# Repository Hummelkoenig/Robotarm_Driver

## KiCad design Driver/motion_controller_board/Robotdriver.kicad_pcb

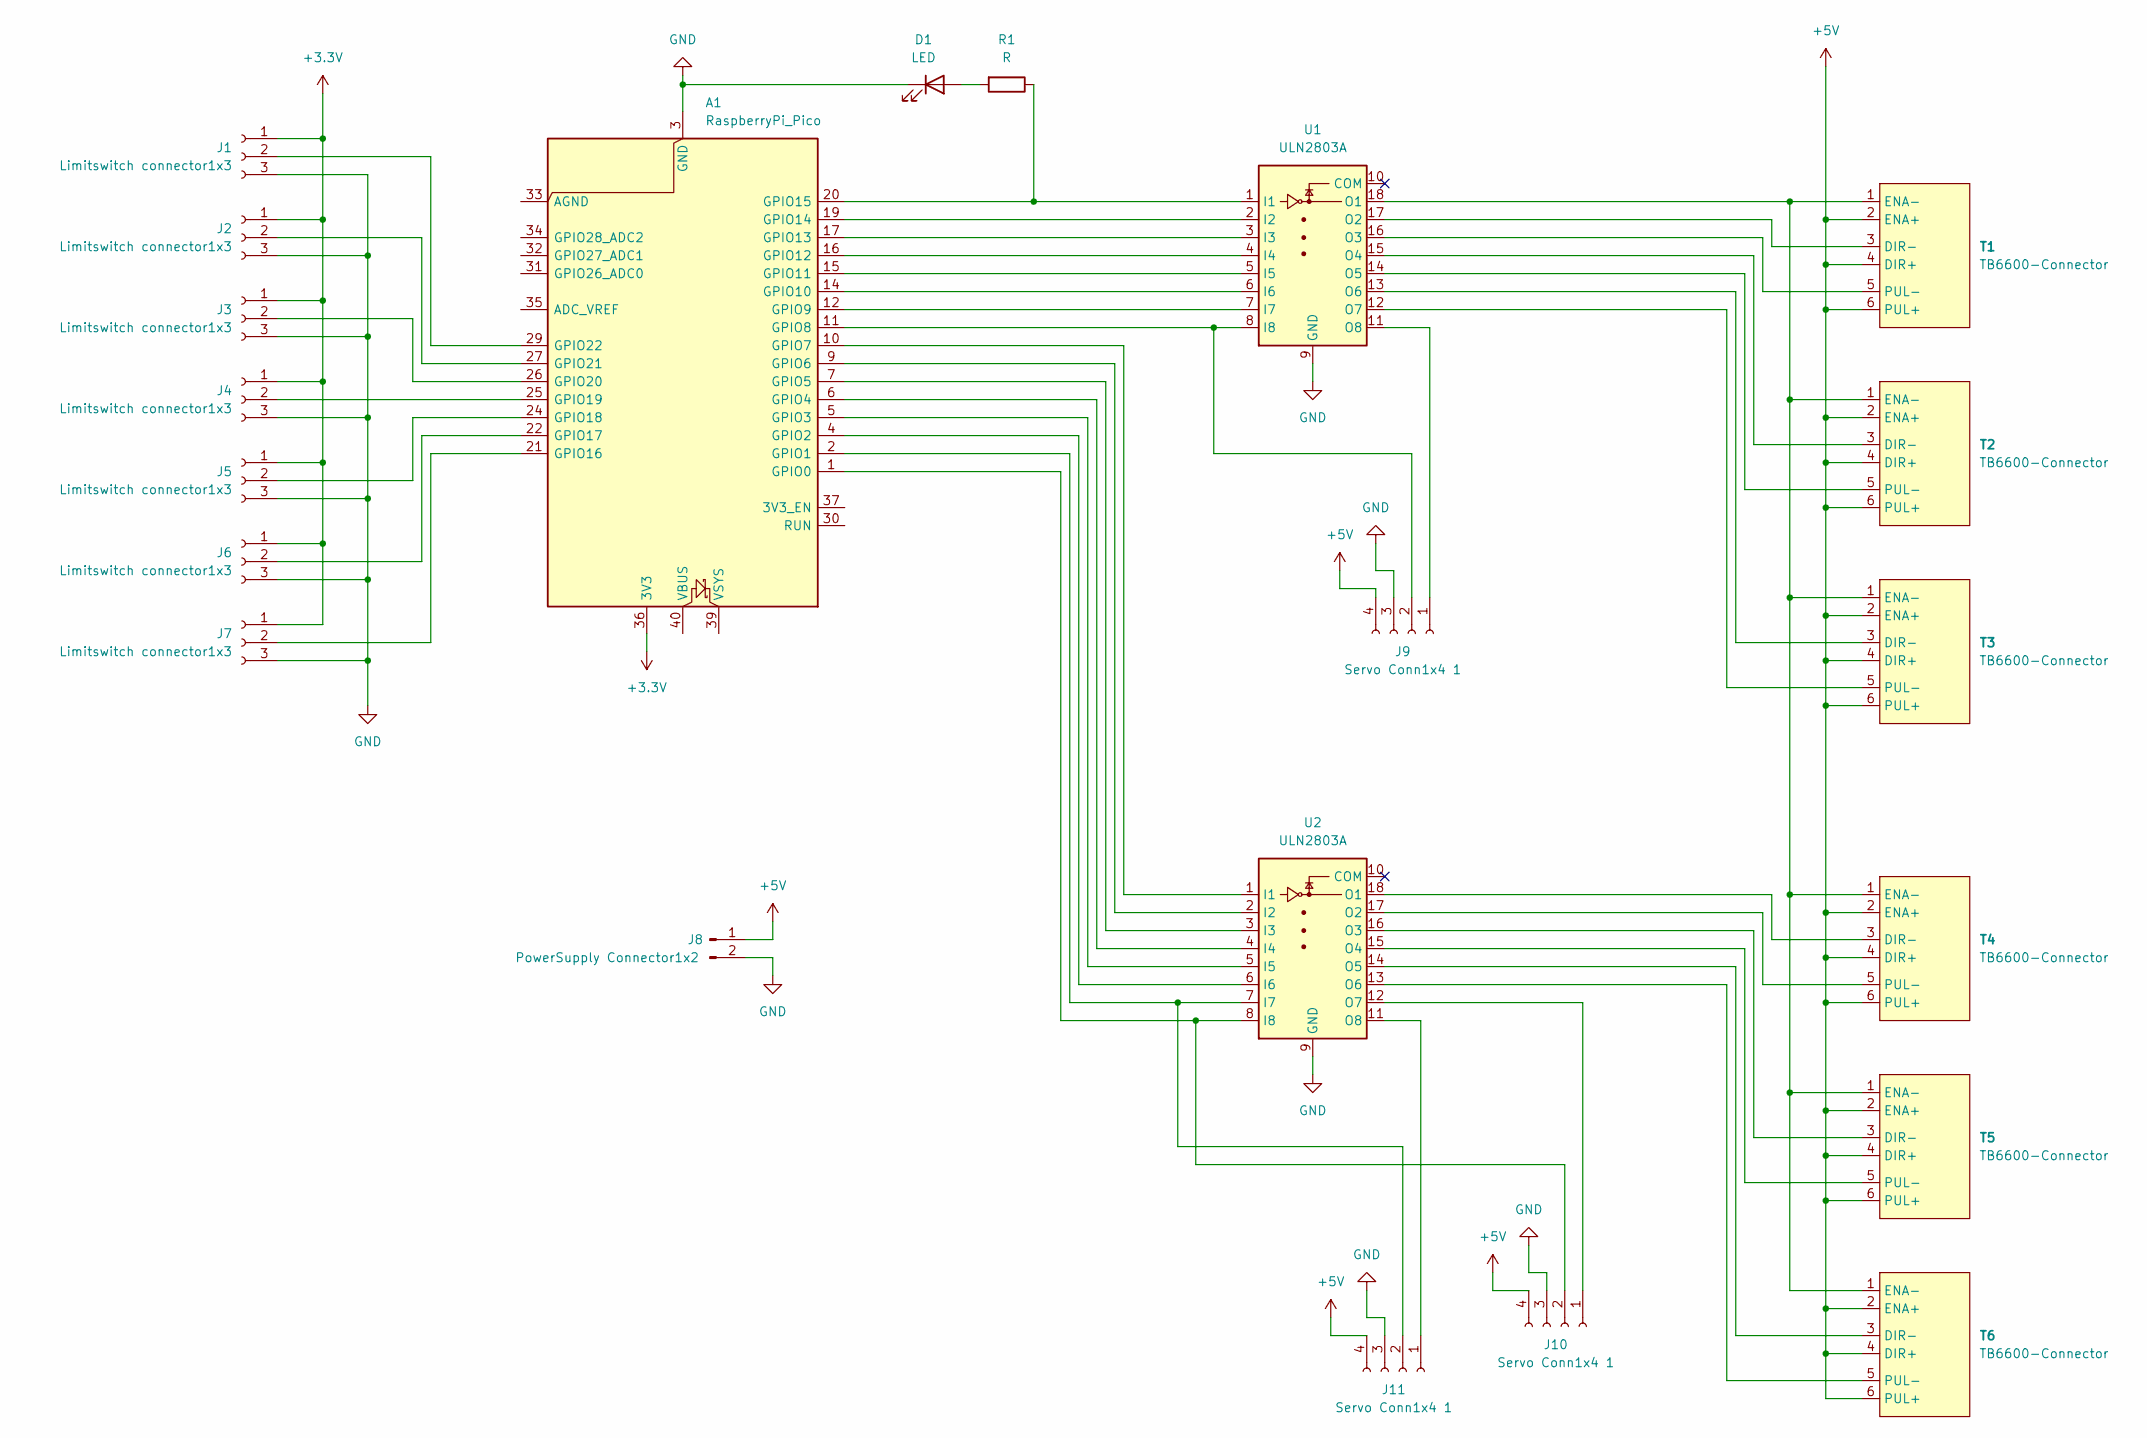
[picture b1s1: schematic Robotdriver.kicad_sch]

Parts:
A1: RaspberryPi_Pico; RaspberryPi_Pico_Common_Unspecified
D1: LED; LED_D5.0mm
J1, J2, J3, J4, J5, J6, J7: Limitswitch connector1x3; JST_EH_B3B-EH-A_1x03_P2.50mm_Vertical
J8: PowerSupply Connector1x2; JST_EH_B2B-EH-A_1x02_P2.50mm_Vertical
J9, J10, J11: Servo Conn1x4 1; JST_EH_B4B-EH-A_1x04_P2.50mm_Vertical
R1: R; R_Axial_DIN0516_L15.5mm_D5.0mm_P20.32mm_Horizontal
T1, T2, T3, T4, T5, T6: TB6600-Connector; JST_EH_B6B-EH-A_1x06_P2.50mm_Vertical
U1, U2: ULN2803A; CERDIP-18_W7.62mm_SideBrazed

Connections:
+3.3V: A1.36 (3V3), J1.1, J2.1, J3.1, J4.1, J5.1, J6.1, J7.1
+5V: J8.1, J9.4, J10.4, J11.4, T1.2 (ENA+), T1.4 (DIR+), T1.6 (PUL+), T2.2 (ENA+), T2.4 (DIR+), T2.6 (PUL+), T3.2 (ENA+), T3.4 (DIR+), T3.6 (PUL+), T4.2 (ENA+), T4.4 (DIR+), T4.6 (PUL+), T5.2 (ENA+), T5.4 (DIR+), T5.6 (PUL+), T6.2 (ENA+), T6.4 (DIR+), T6.6 (PUL+)
GND: A1.3 (GND), A1.8 (GND), A1.13 (GND), A1.18 (GND), A1.23 (GND), A1.28 (GND), A1.38 (GND), D1.1 (K), J1.3, J2.3, J3.3, J4.3, J5.3, J6.3, J7.3, J8.2, J9.3, J10.3, J11.3, U1.9 (GND), U2.9 (GND)
unnamed: A1.1 (GPIO0), J10.2, U2.8 (I8)
unnamed: A1.2 (GPIO1), J11.2, U2.7 (I7)
unnamed: A1.4 (GPIO2), U2.6 (I6)
unnamed: A1.5 (GPIO3), U2.5 (I5)
unnamed: A1.6 (GPIO4), U2.4 (I4)
unnamed: A1.7 (GPIO5), U2.3 (I3)
unnamed: A1.9 (GPIO6), U2.2 (I2)
unnamed: A1.10 (GPIO7), U2.1 (I1)
unnamed: A1.11 (GPIO8), J9.2, U1.8 (I8)
unnamed: A1.12 (GPIO9), U1.7 (I7)
unnamed: A1.14 (GPIO10), U1.6 (I6)
unnamed: A1.15 (GPIO11), U1.5 (I5)
unnamed: A1.16 (GPIO12), U1.4 (I4)
unnamed: A1.17 (GPIO13), U1.3 (I3)
unnamed: A1.19 (GPIO14), U1.2 (I2)
unnamed: A1.20 (GPIO15), R1.1, U1.1 (I1)
unnamed: A1.21 (GPIO16), J7.2
unnamed: A1.22 (GPIO17), J6.2
unnamed: A1.24 (GPIO18), J5.2
unnamed: A1.25 (GPIO19), J4.2
unnamed: A1.26 (GPIO20), J3.2
unnamed: A1.27 (GPIO21), J2.2
unnamed: A1.29 (GPIO22), J1.2
unnamed: D1.2 (A), R1.2
unnamed: J9.1, U1.11 (O8)
unnamed: J10.1, U2.12 (O7)
unnamed: J11.1, U2.11 (O8)
unnamed: T1.3 (DIR-), U1.17 (O2)
unnamed: T1.1 (ENA-), T2.1 (ENA-), T3.1 (ENA-), T4.1 (ENA-), T5.1 (ENA-), T6.1 (ENA-), U1.18 (O1)
unnamed: T1.5 (PUL-), U1.16 (O3)
unnamed: T2.3 (DIR-), U1.15 (O4)
unnamed: T2.5 (PUL-), U1.14 (O5)
unnamed: T3.3 (DIR-), U1.13 (O6)
unnamed: T3.5 (PUL-), U1.12 (O7)
unnamed: T4.3 (DIR-), U2.18 (O1)
unnamed: T4.5 (PUL-), U2.17 (O2)
unnamed: T5.3 (DIR-), U2.16 (O3)
unnamed: T5.5 (PUL-), U2.15 (O4)
unnamed: T6.3 (DIR-), U2.14 (O5)
unnamed: T6.5 (PUL-), U2.13 (O6)

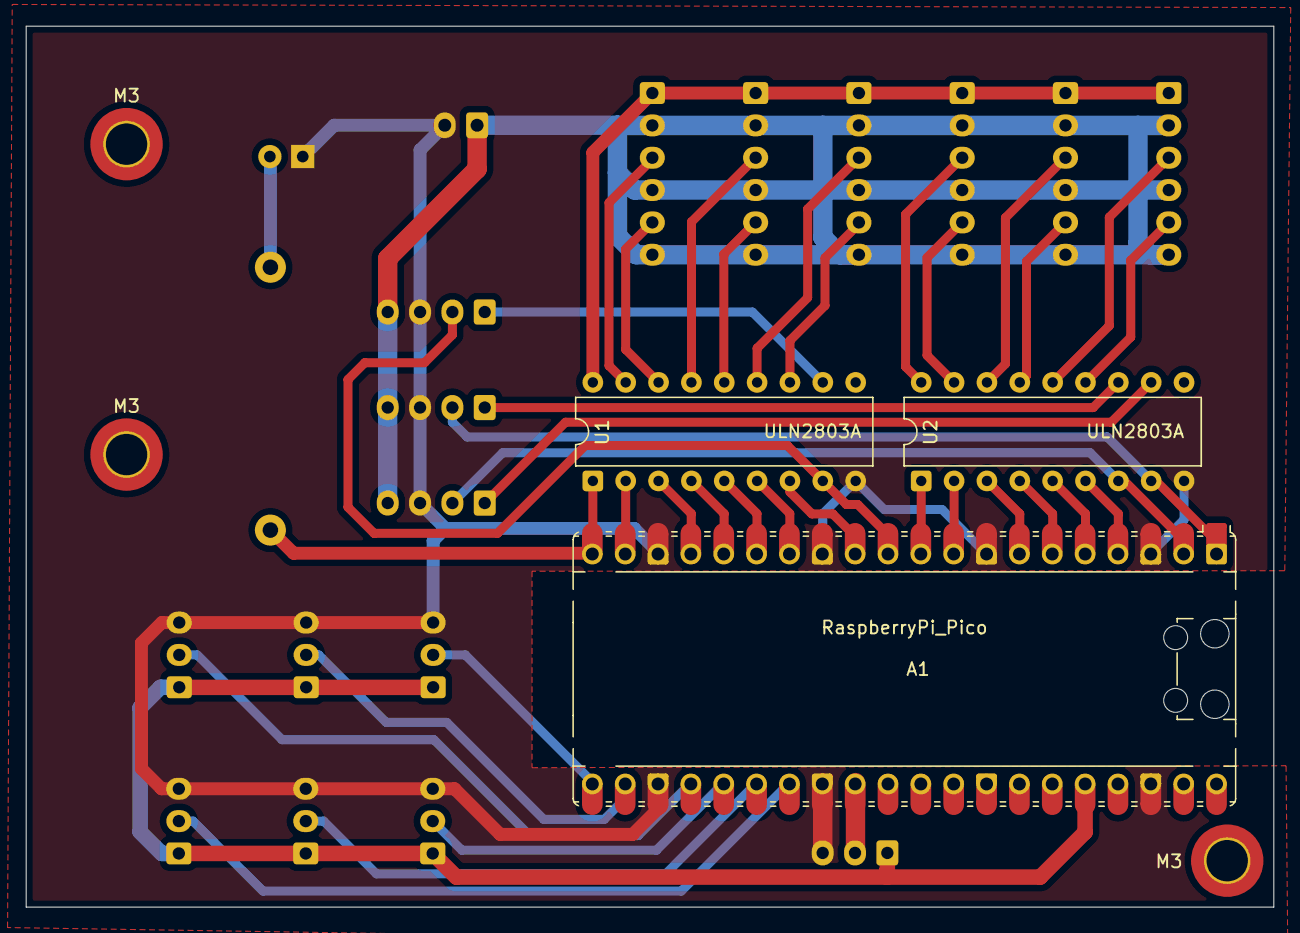
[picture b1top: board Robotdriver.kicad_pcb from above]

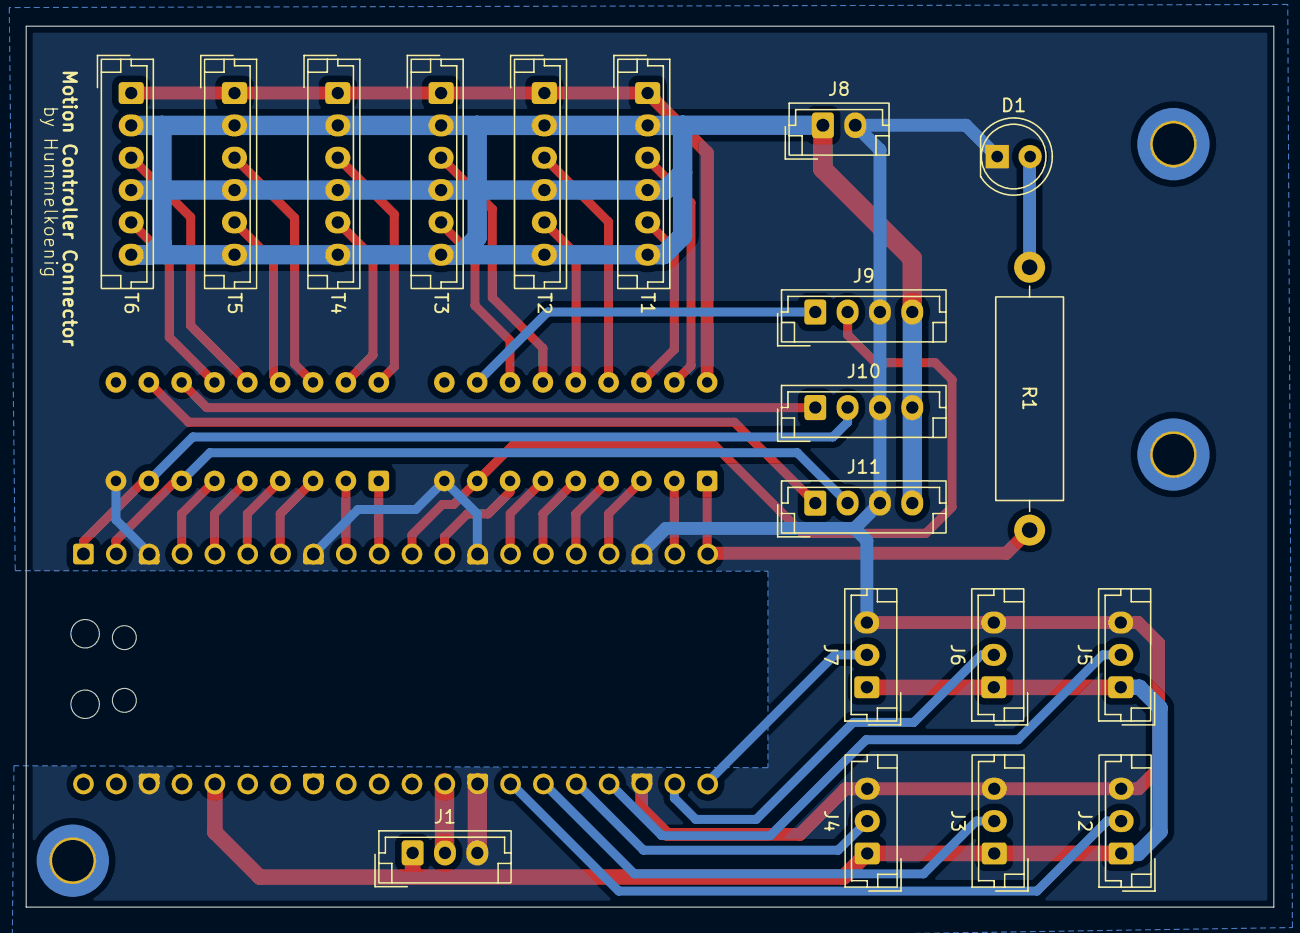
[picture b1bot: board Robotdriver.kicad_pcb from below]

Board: 2 copper layers, 96.5 x 68.1 mm, 25 parts (19 on the bottom side), 43 nets.

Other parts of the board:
M3, M3#2, M3#3: MountingHole_3.2mm_M3_DIN965_Pad_TopBottom
